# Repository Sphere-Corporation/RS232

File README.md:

</img>
<h3 style="text-align: center;">Project ARC - Additional RS-232 Circuitry</h3>

## Introduction

This project (Project ARC) is a spin-off from my Sphere-1 reconstruction project, in that it provides additional functionality (in the form of an RS-232 interface) which was not present on the original CPU/2 board. 

Additional components would need to be purchased.

This project aims to make adding RS-232 capability to the CPU/2 board simpler and more modular in its approach.

The documentation is stored on Google Docs for reference - the link is below.

## Documentation

[History and Description of the project](https://drive.google.com/drive/folders/1ViCCd09BQsjbNeUuYninBBR5Ygf1v3um?usp=sharing)

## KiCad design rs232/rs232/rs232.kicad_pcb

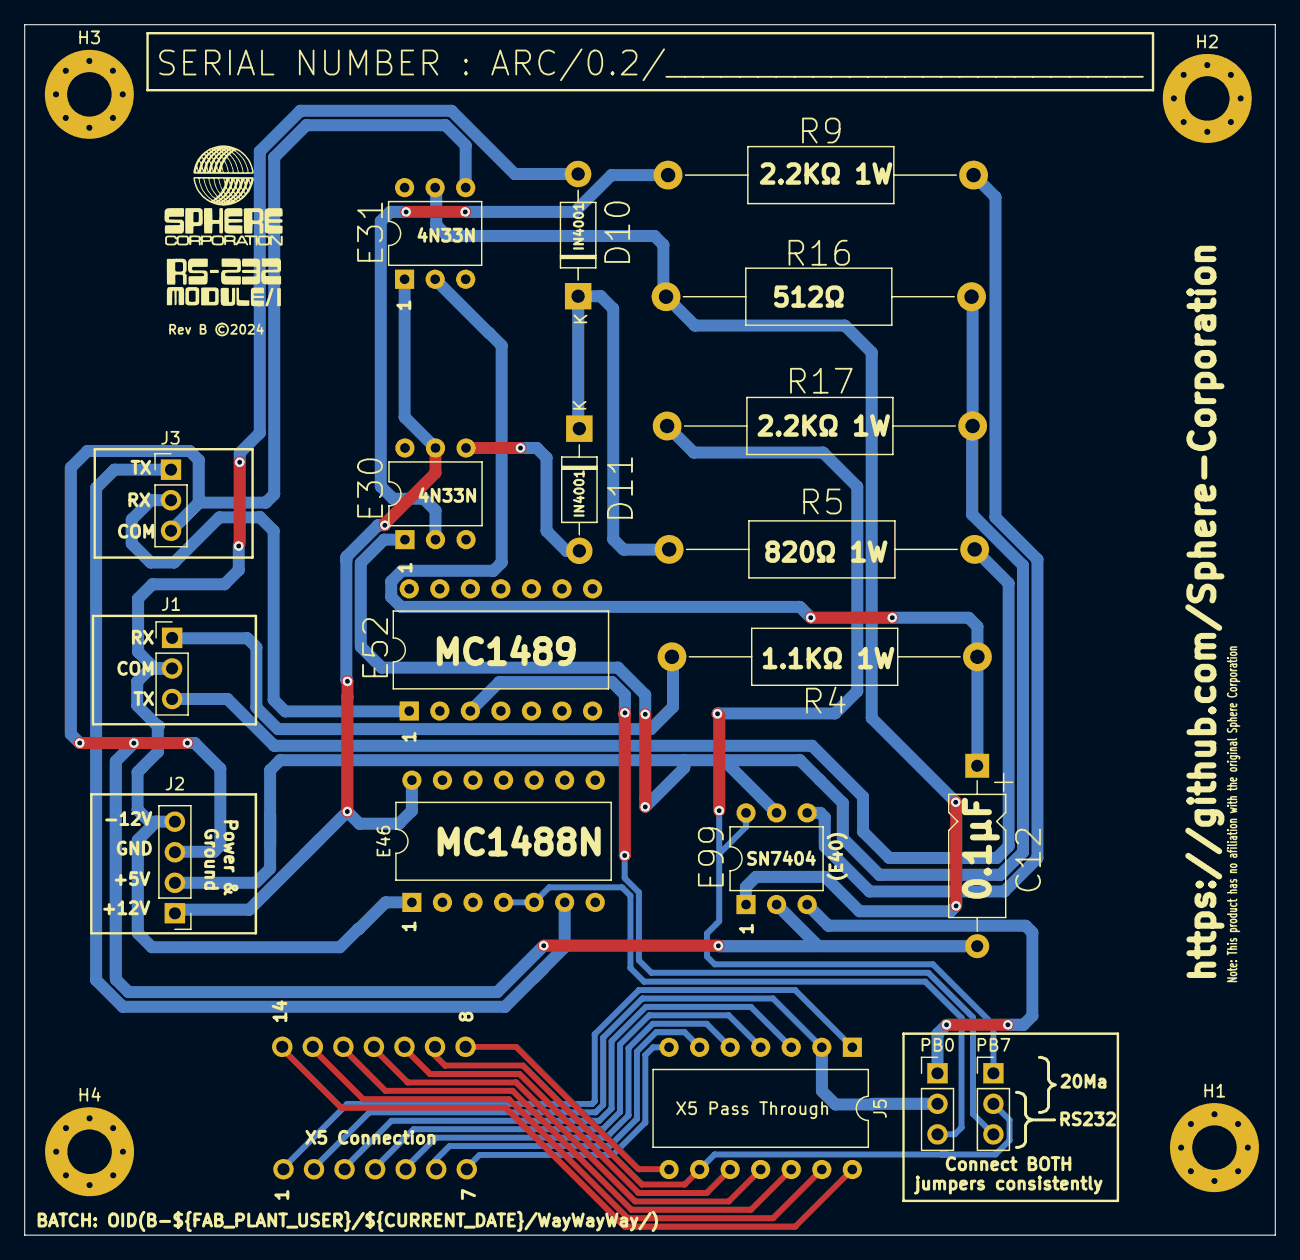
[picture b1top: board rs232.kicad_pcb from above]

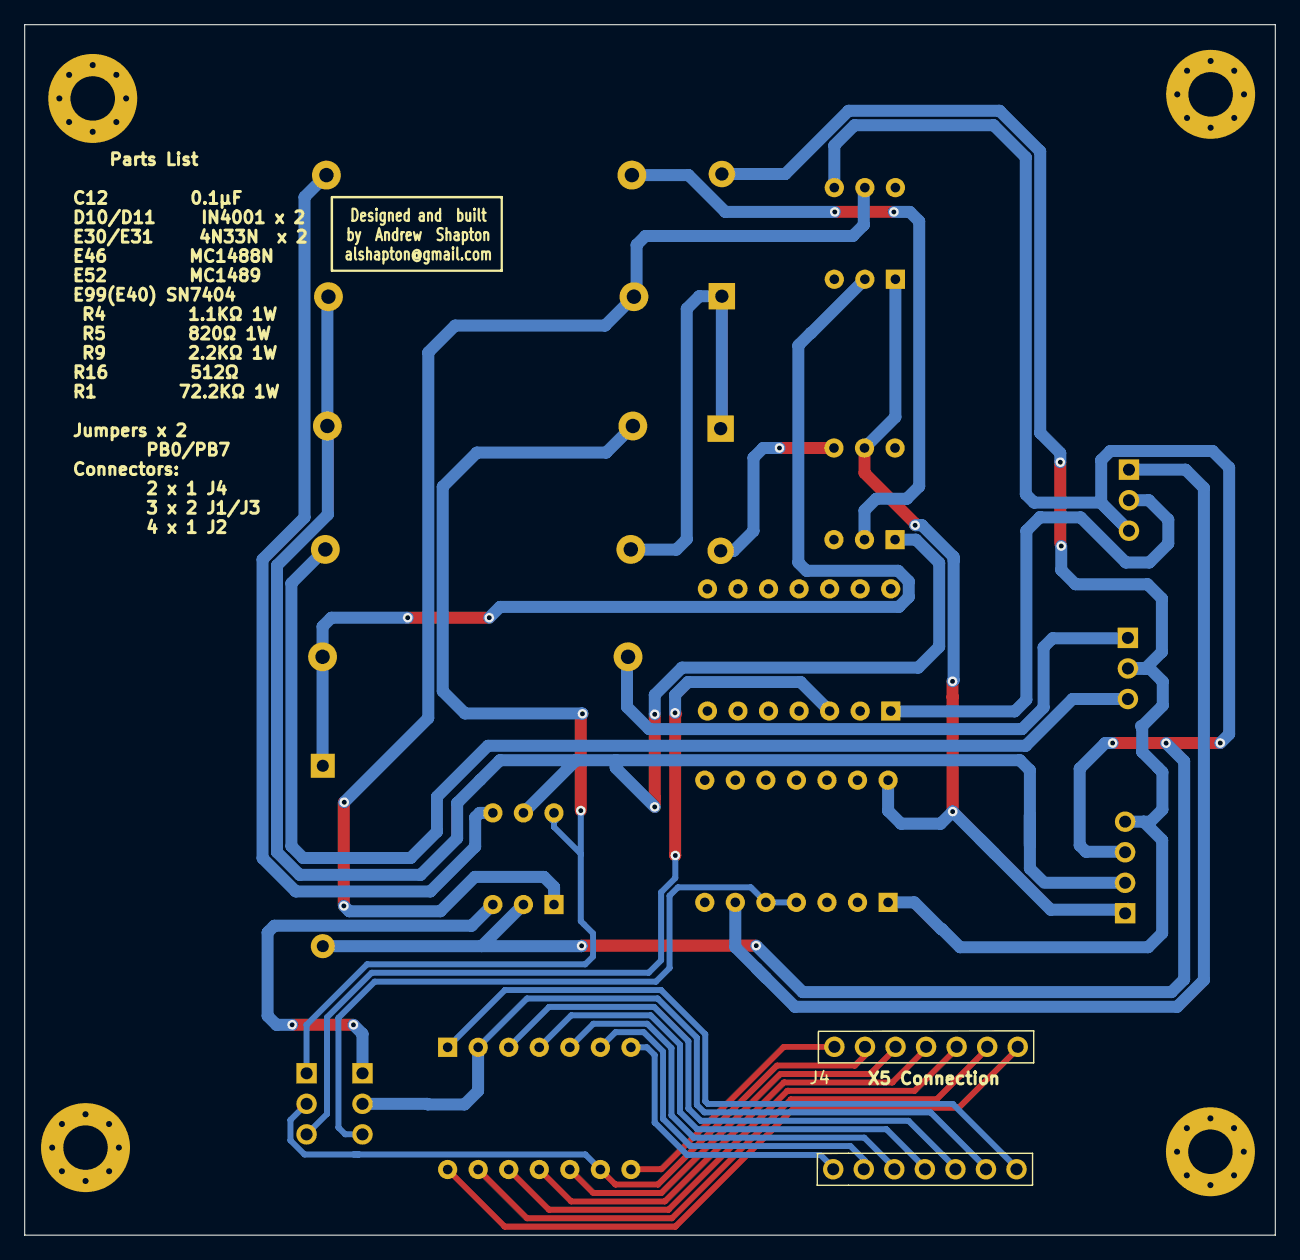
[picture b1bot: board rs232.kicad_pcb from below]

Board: 2 copper layers, 104.0 x 100.7 mm, 25 parts (2 on the bottom side), 32 nets.

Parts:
C12: CK-104; CP_Axial_L10.0mm_D4.5mm_P15.00mm_Horizontal
D10, D11: 1N4001; D_DO-41_SOD81_P10.16mm_Horizontal
E30, E31: 4N33N; DIP-6_W7.62mm
E46: MC1488N; DIP-14_W10.16mm
E52: MC1489; DIP-14_W10.16mm
E99: SN7404; DIP-6_W7.62mm
H1, H2, H3, H4: MountingHole_Pad; MountingHole_3.7mm_Pad_Via
J1, J3: Conn_01x03_Pin; PinHeader_1x03_P2.54mm_Vertical
J2: Conn_01x04_Pin; PinHeader_1x04_P2.54mm_Vertical
J4, J6: Conn_01x03_Pin; PinHeader_1x07_P2.54mm_Vertical
J5: X5 Pass Through; DIP-14_W10.16mm
PB0, PB7: Jumper_3_Bridged12; PinHeader_1x03_P2.54mm_Vertical
R4: 1.1 kOhm 1W; R_Axial_DIN0414_L11.9mm_D4.5mm_P25.40mm_Horizontal
R5: 820 Ohm 1W; R_Axial_DIN0414_L11.9mm_D4.5mm_P25.40mm_Horizontal
R9: 2 kOhm ¼W; R_Axial_DIN0414_L11.9mm_D4.5mm_P25.40mm_Horizontal
R16: 512 Ohm ¼W; R_Axial_DIN0414_L11.9mm_D4.5mm_P25.40mm_Horizontal
R17: 1 kOhm ¼W; R_Axial_DIN0414_L11.9mm_D4.5mm_P25.40mm_Horizontal

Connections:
unnamed: C12.1, E31.2 (C), R4.1
unnamed: D10.2 (A), E46.1 (V_{CC}-), J1.2, J2.4
unnamed: D10.1 (K), D11.1 (K), R5.1
unnamed: D11.2 (A), E30.4 (E)
unnamed: E30.1 (A), E99.5 (V_{CC}), J2.2, R16.2, R17.2
unnamed: E30.2 (C), R9.1
unnamed: E30.5 (C), E31.1 (A), E46.14 (V_{CC}+), J2.1
unnamed: C12.2, E31.4 (E), E99.2 (GND), J2.3, J3.3
unnamed: E46.4 (2A), E46.5 (2B), PB0.3 (B)
unnamed: E46.6 (2Y), J3.1
unnamed: E52.1 (1A), J3.2
unnamed: E52.3 (1Y), PB7.3 (B)
unnamed: E31.5 (C), E99.1 (1A), R16.1
unnamed: E99.6 (1Y), PB7.1 (A), R17.1
unnamed: E99.3 (2A), PB0.1 (A)
unnamed: E99.4 (2Y), R9.2
unnamed: J1.1, R4.2
unnamed: J1.3, R5.2
unnamed: J4.7, J5.1
unnamed: J4.6, J5.2, PB0.2 (C)
unnamed: J4.5, J5.3
unnamed: J4.4, J5.4
unnamed: J4.3, J5.5
unnamed: J4.2, J5.6
unnamed: J4.1, J5.7
unnamed: J5.8, J6.1
unnamed: J5.9, J6.2, PB7.2 (C)
unnamed: J5.10, J6.3
unnamed: J5.11, J6.4
unnamed: J5.12, J6.5
unnamed: J5.13, J6.6
unnamed: J5.14, J6.7

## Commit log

2023-09-28 Updated gitignore
    Now ignores backup files
2024-04-02 Final commit before disassociating from combined repo
2024-12-23 Initial commit of rebased-repo
2024-12-23 Updated documentation and readme page

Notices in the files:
rs232/rs232/rs232.kicad_pcb:
Rev B ©2024
